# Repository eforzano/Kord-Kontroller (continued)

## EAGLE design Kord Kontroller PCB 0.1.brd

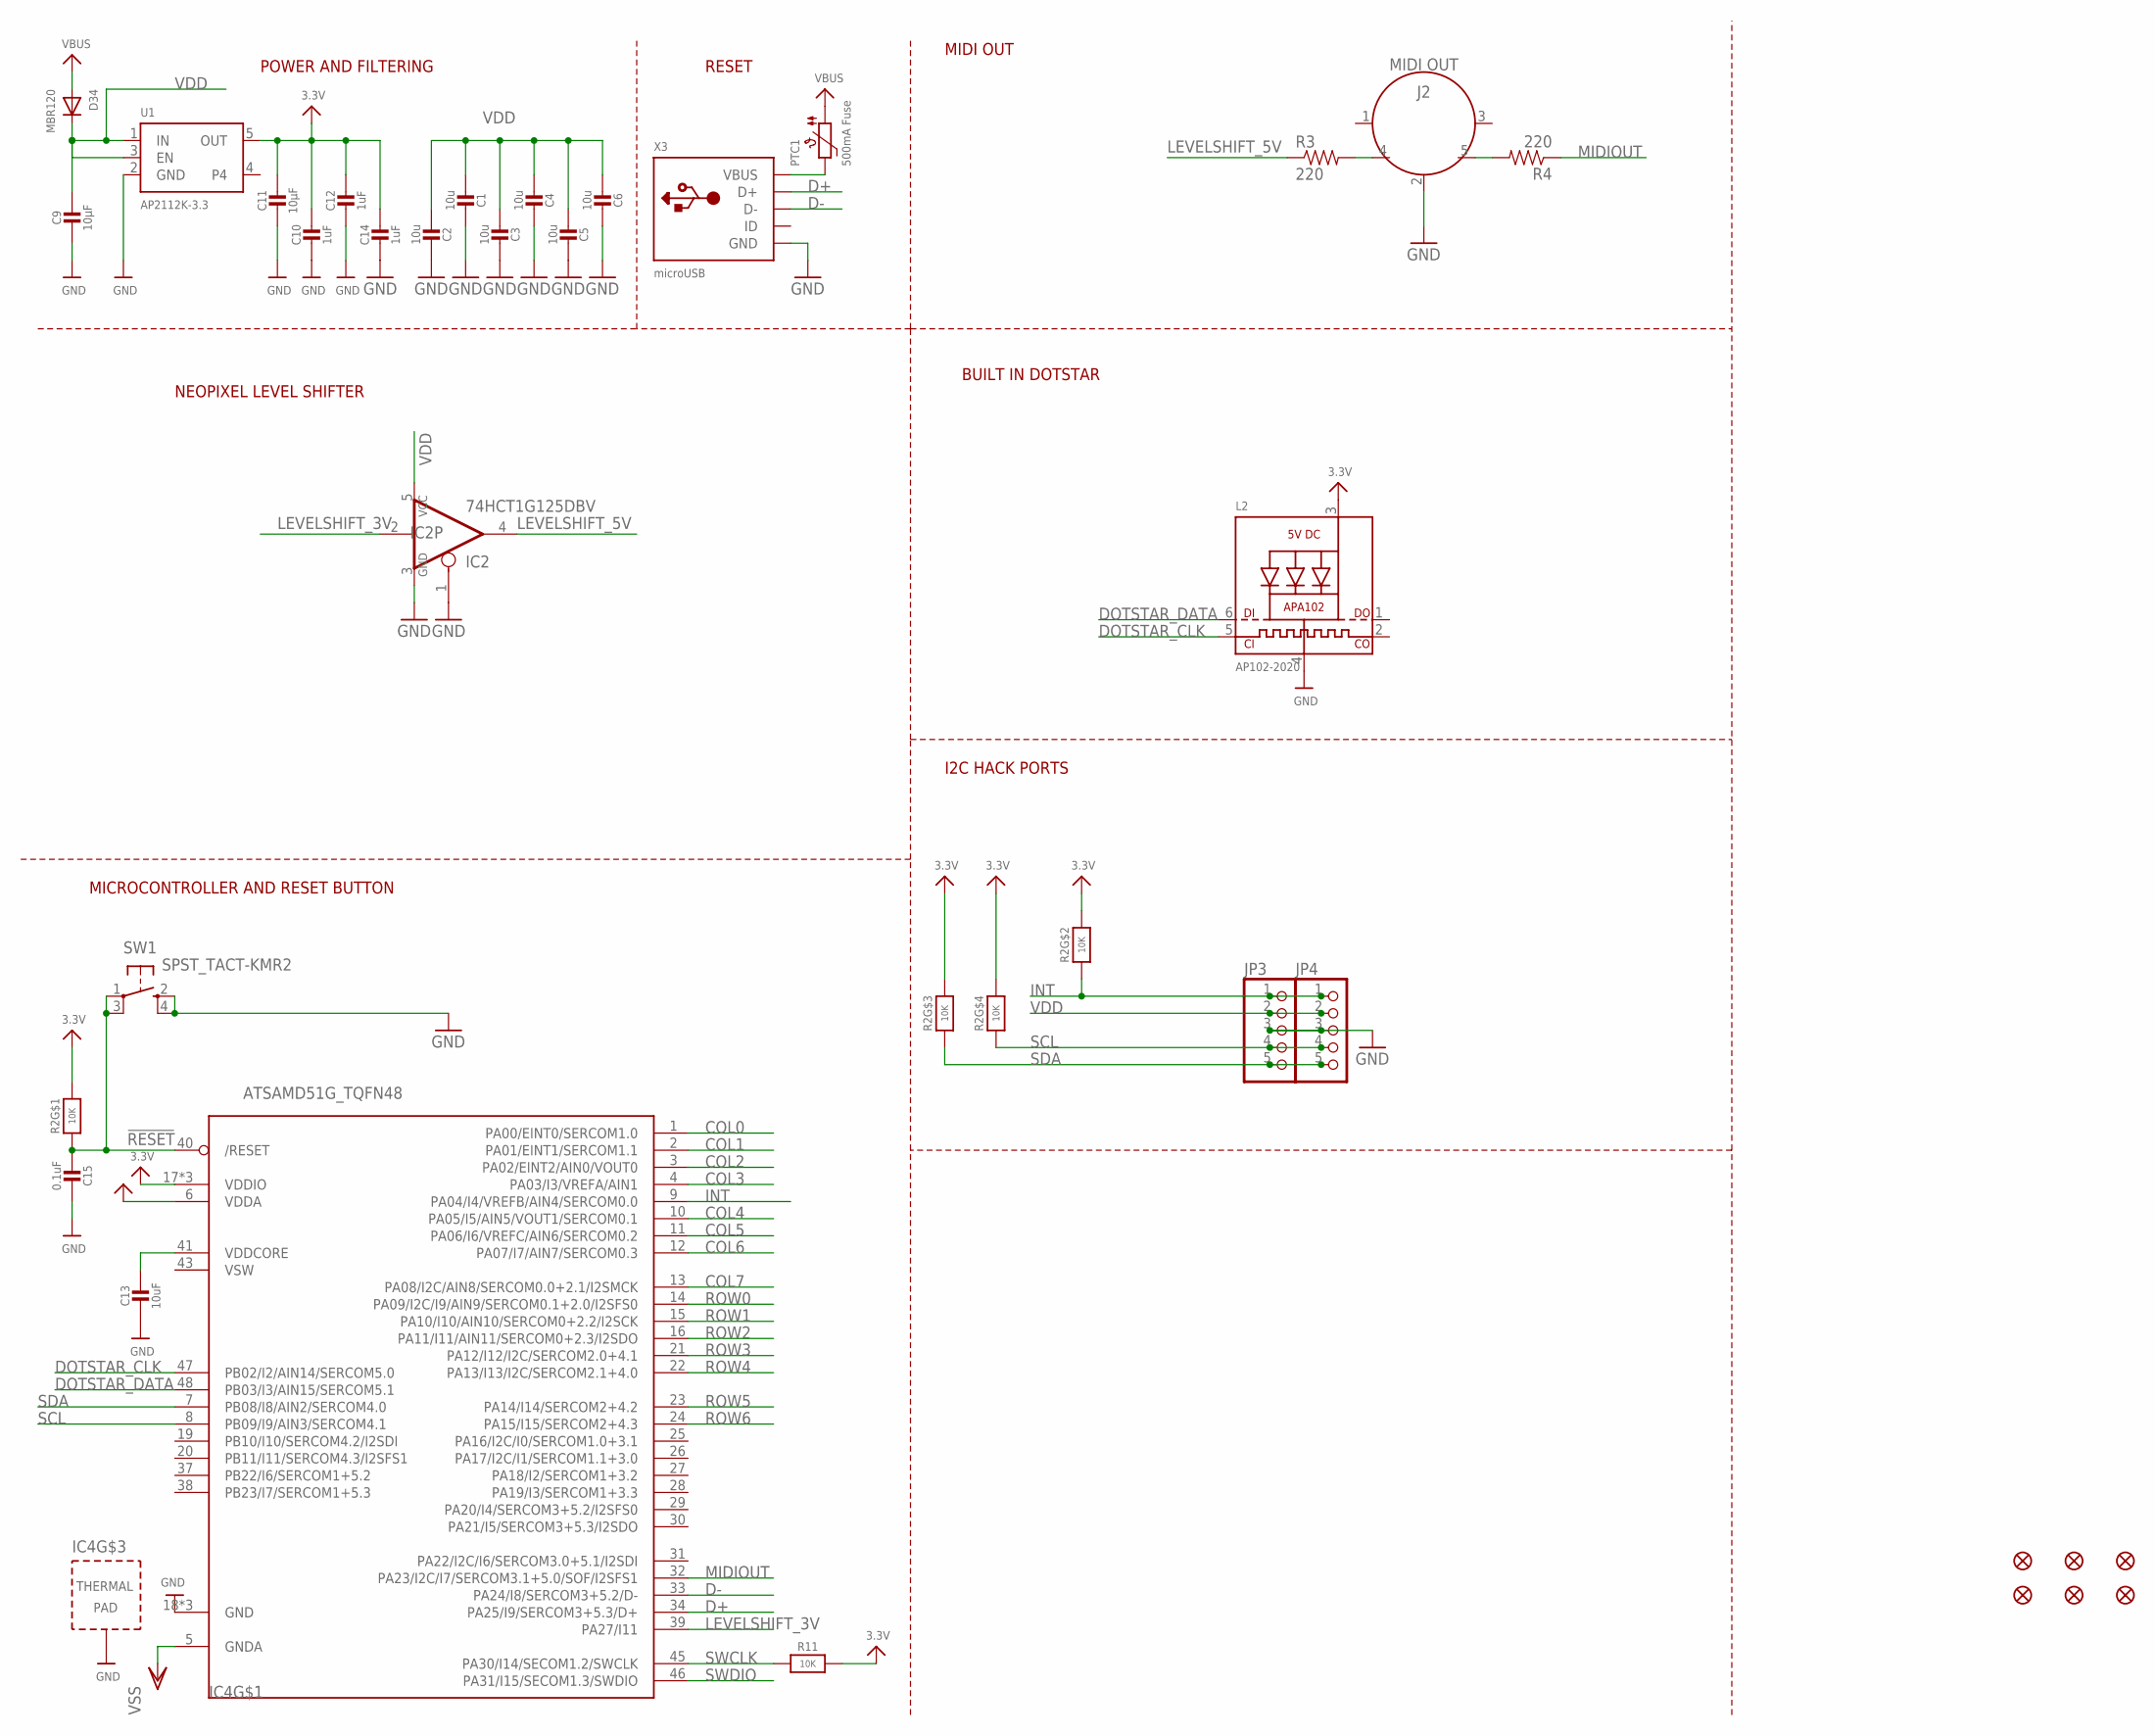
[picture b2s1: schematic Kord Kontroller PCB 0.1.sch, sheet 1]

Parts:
C1, C2, C3, C4, C5, C6: 10u; 0805-NO
C9, C11: 10µF; 0805-NO
C10, C12, C14: 1uF; 0603-NO
C13: 10uF; 0805-NO
C15: 0.1uF; 0603-NO
D34: MBR120; SOD-123FL
FID1, FID2, FID3, FID4, FID5, FID6: FIDUCIAL_1MM
IC2: 74HCT1G125DBV; SOT23-5
IC4: ATSAMD51G_TQFN48; TQFN48_7MM
J2: MIDI OUT; 5-PIN-DIN-RA-PCB-NEW
JP3, JP4: HEADER-1X5EDGESMT; 5P_EDGECONNECT
L2: AP102-2020; APA102_2020
PTC1: 500mA Fuse; 1206
R2: 10K; RESPACK_4X0603
R3, R4: 220; 0603-RES
R11: 10K; 0603-NO
SW1: SPST_TACT-KMR2; KMR2
U1: AP2112K-3.3; SOT23-5
X3: microUSB; 4UCONN_20329_NARROW

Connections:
3.3V: C10.1, C11.1, C12.1, C14.1, IC4.17 (VDDIO), IC4.36 (VDDIO), IC4.44 (VDDIO), L2.3 (VDD), R2.5 (2), R2.6 (2), R2.7 (2), R2.8 (2), R11.2, U1.5 (OUT)
!RESET: C15.2, IC4.40 (/RESET), R2.1, SW1.1, SW1.3 (P1)
AVDD: IC4.6 (VDDA)
COL0: IC4.1 (PA00/EINT0/SERCOM1.0); also elsewhere on the board
COL1: IC4.2 (PA01/EINT1/SERCOM1.1); also elsewhere on the board
COL2: IC4.3 (PA02/EINT2/AIN0/VOUT0); also elsewhere on the board
COL3: IC4.4 (PA03/I3/VREFA/AIN1); also elsewhere on the board
COL4: IC4.10 (PA05/I5/AIN5/VOUT1/SERCOM0.1); also elsewhere on the board
COL5: IC4.11 (PA06/I6/VREFC/AIN6/SERCOM0.2); also elsewhere on the board
COL6: IC4.12 (PA07/I7/AIN7/SERCOM0.3); also elsewhere on the board
COL7: IC4.13 (PA08/I2C/AIN8/SERCOM0.0+2.1/I2SMCK); also elsewhere on the board
D+: IC4.34 (PA25/I9/SERCOM3+5.3/D+), X3.D+
D-: IC4.33 (PA24/I8/SERCOM3+5.2/D-), X3.D-
DOTSTAR_CLK: IC4.47 (PB02/I2/AIN14/SERCOM5.0), L2.5 (CKI)
DOTSTAR_DATA: IC4.48 (PB03/I3/AIN15/SERCOM5.1), L2.6 (DI)
GND: C1.1, C2.1, C3.1, C4.1, C5.1, C6.1, C9.2, C10.2, C11.2, C12.2, C13.2, C14.2, C15.1, IC2.1 (OE), IC2.3 (GND), IC4.18 (GND), IC4.35 (GND), IC4.42 (GND), IC4.THERMAL (TP), J2.2, JP3.3, JP4.3, L2.4 (GND), SW1.2 (S), SW1.4 (S1), U1.2 (GND), X3.BASE@1 (GND), X3.BASE@2 (GND), X3.GND, X3.SPRT@1 (GND), X3.SPRT@2 (GND), X3.SPRT@3 (GND), X3.SPRT@4 (GND); also elsewhere on the board
INT: IC4.9 (PA04/I4/VREFB/AIN4/SERCOM0.0), JP3.1, JP4.1, R2.2 (1)
unnamed: PTC1.2, X3.VBUS
NEOPIXEL_3V: IC2.2 (I), IC4.39 (PA27/I11); also elsewhere on the board
unnamed: IC2.4 (O), R3.1
unnamed: J2.4, R3.2
unnamed: J2.5, R4.2
unnamed: IC4.32 (PA23/I2C/I7/SERCOM3.1+5.0/SOF/I2SFS1), R4.1
ROW0: IC4.14 (PA09/I2C/I9/AIN9/SERCOM0.1+2.0/I2SFS0); also elsewhere on the board
ROW1: IC4.15 (PA10/I10/AIN10/SERCOM0+2.2/I2SCK); also elsewhere on the board
ROW2: IC4.16 (PA11/I11/AIN11/SERCOM0+2.3/I2SDO); also elsewhere on the board
ROW3: IC4.21 (PA12/I12/I2C/SERCOM2.0+4.1); also elsewhere on the board
ROW4: IC4.22 (PA13/I13/I2C/SERCOM2.1+4.0); also elsewhere on the board
ROW5: IC4.23 (PA14/I14/SERCOM2+4.2); also elsewhere on the board
ROW6: IC4.24 (PA15/I15/SERCOM2+4.3); also elsewhere on the board
SCL: IC4.8 (PB09/I9/AIN3/SERCOM4.1), JP3.4, JP4.4, R2.4 (1)
SDA: IC4.7 (PB08/I8/AIN2/SERCOM4.0), JP3.5, JP4.5, R2.3 (1)
SWCLK: IC4.45 (PA30/I14/SECOM1.2/SWCLK), R11.1
SWDIO: IC4.46 (PA31/I15/SECOM1.3/SWDIO)
VBUS: D34.A, PTC1.1
VDD: C1.2, C2.2, C3.2, C4.2, C5.2, C6.2, C9.1, D34.C, IC2.5 (VCC), JP3.2, JP4.2, U1.1 (IN), U1.3 (EN); also elsewhere on the board
VDDCORE: C13.1, IC4.41 (VDDCORE)
VSS: IC4.5 (GNDA)
VSW: IC4.43 (VSW)

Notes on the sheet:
POWER AND FILTERING
RESET
BUILT IN DOTSTAR
I2C HACK PORTS
MICROCONTROLLER AND RESET BUTTON
MIDI OUT
NEOPIXEL LEVEL SHIFTER

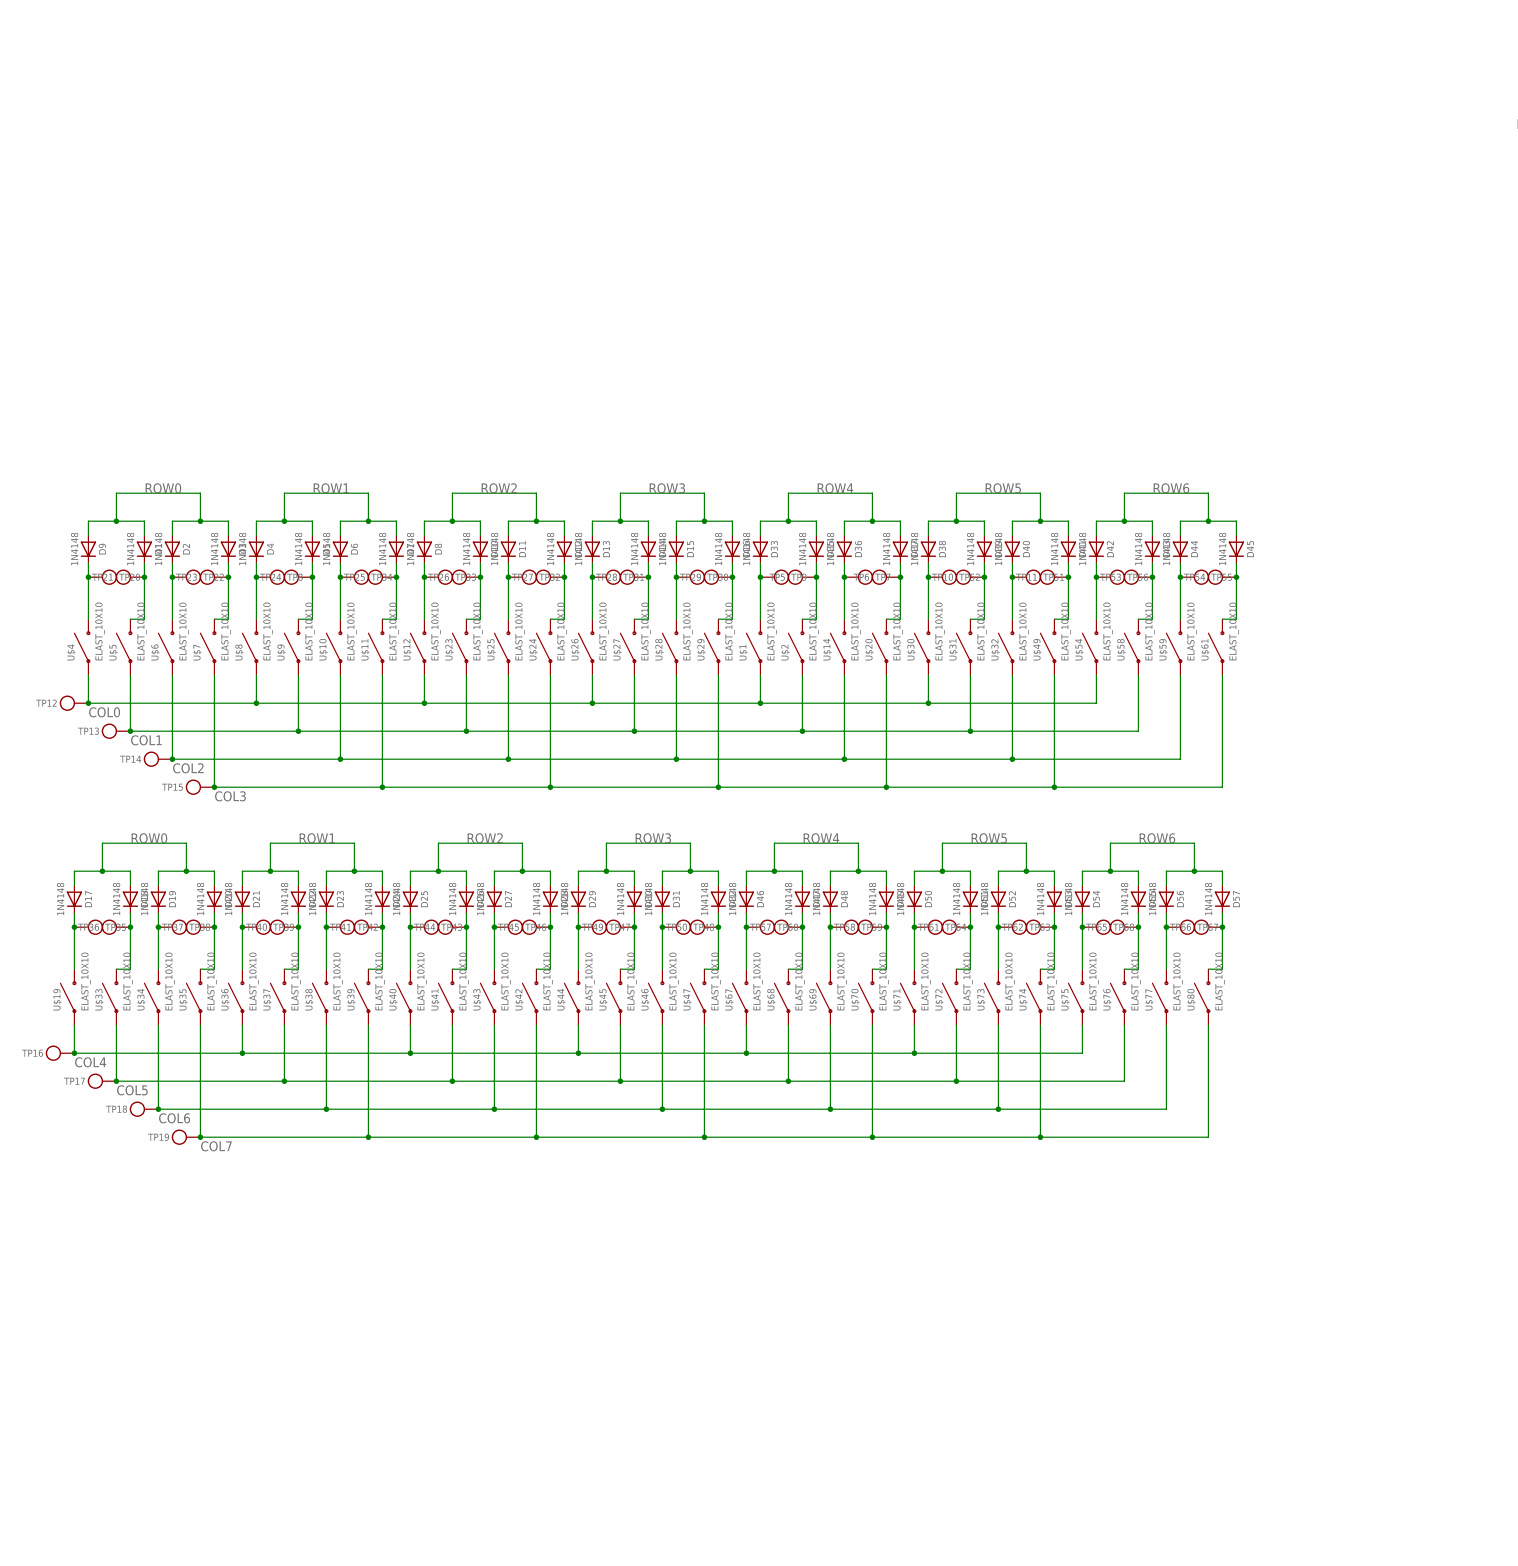
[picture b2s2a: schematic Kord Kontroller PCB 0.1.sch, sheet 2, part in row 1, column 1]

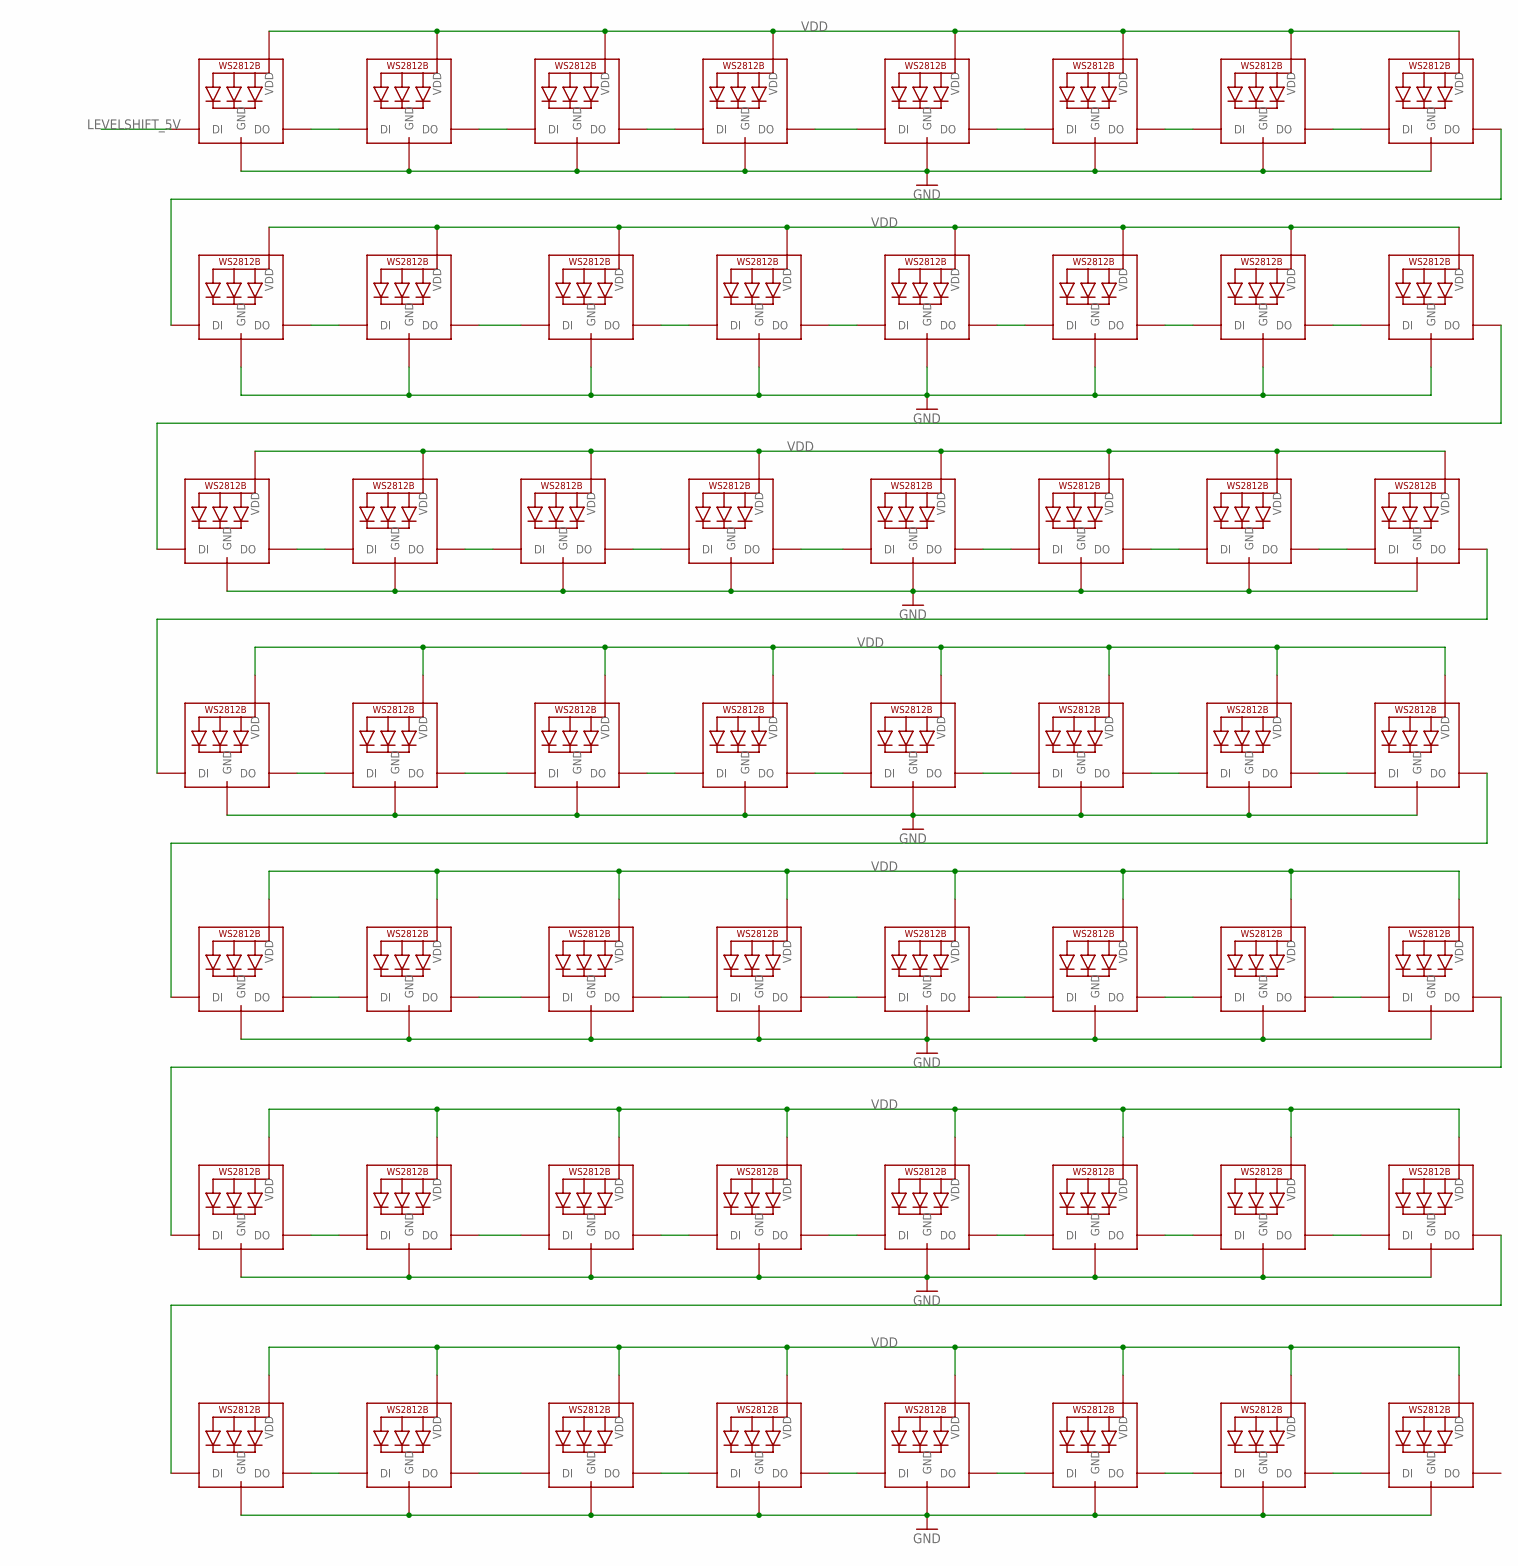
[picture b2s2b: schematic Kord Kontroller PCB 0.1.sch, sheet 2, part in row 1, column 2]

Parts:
D1, D2, D3, D4, D5, D6, D7, D8, D9, D10, D11, D12, D13, D14, D15, D16, D17, D18, D19, D20, D21, D22, D23, D24, D25, D26, D27, D28, D29, D30, D31, D32, D33, D35, D36, D37, D38, D39, D40, D41, D42, D43, D44, D45, D46, D47, D48, D49, D50, D51, D52, D53, D54, D55, D56, D57: 1N4148; SOD-323
LED1, LED2, LED3, LED4, LED5, LED6, LED7, LED8, LED9, LED10, LED11, LED12, LED13, LED14, LED15, LED16, LED17, LED18, LED19, LED20, LED21, LED22, LED23, LED24, LED25, LED26, LED27, LED28, LED29, LED30, LED31, LED32, LED33, LED34, LED35, LED36, LED37, LED38, LED39, LED40, LED41, LED42, LED43, LED44, LED45, LED46, LED47, LED48, LED49, LED50, LED51, LED52, LED53, LED54, LED55, LED56: WS2812B3535; LED3535
TP5, TP6, TP7, TP8, TP9, TP10, TP11, TP12, TP13, TP14, TP15, TP16, TP17, TP18, TP19, TP20, TP21, TP22, TP23, TP24, TP25, TP26, TP27, TP28, TP29, TP30, TP31, TP32, TP33, TP34, TP35, TP36, TP37, TP38, TP39, TP40, TP41, TP42, TP43, TP44, TP45, TP46, TP47, TP48, TP49, TP50, TP51, TP52, TP53, TP54, TP55, TP56, TP57, TP58, TP59, TP60, TP61, TP62, TP63, TP64, TP65, TP66, TP67, TP68: TESTPOINTROUND1.5MM; TESTPOINT_ROUND_1.5MM
U$1, U$2, U$4, U$5, U$6, U$7, U$8, U$9, U$10, U$11, U$12, U$14, U$19, U$20, U$23, U$24, U$25, U$26, U$27, U$28, U$29, U$30, U$31, U$32, U$33, U$34, U$35, U$36, U$37, U$38, U$39, U$40, U$41, U$42, U$43, U$44, U$45, U$46, U$47, U$49, U$54, U$58, U$59, U$61, U$67, U$68, U$69, U$70, U$71, U$72, U$73, U$74, U$75, U$76, U$77, U$80: ELAST_10X10; ELAST_PAD_SQUARE_10MM_4X4WIDE

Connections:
COL0: TP12.P$1, U$1.P$1, U$4.P$1, U$8.P$1, U$12.P$1, U$26.P$1, U$30.P$1, U$54.P$1; also elsewhere on the board
COL1: TP13.P$1, U$2.P$1, U$5.P$1, U$9.P$1, U$23.P$1, U$27.P$1, U$31.P$1, U$58.P$1; also elsewhere on the board
COL2: TP14.P$1, U$6.P$1, U$10.P$1, U$14.P$1, U$25.P$1, U$28.P$1, U$32.P$1, U$59.P$1; also elsewhere on the board
COL3: TP15.P$1, U$7.P$1, U$11.P$1, U$20.P$1, U$24.P$1, U$29.P$1, U$49.P$1, U$61.P$1; also elsewhere on the board
COL4: TP16.P$1, U$19.P$1, U$36.P$1, U$40.P$1, U$44.P$1, U$67.P$1, U$71.P$1, U$75.P$1; also elsewhere on the board
COL5: TP17.P$1, U$33.P$1, U$37.P$1, U$41.P$1, U$45.P$1, U$68.P$1, U$72.P$1, U$76.P$1; also elsewhere on the board
COL6: TP18.P$1, U$34.P$1, U$38.P$1, U$43.P$1, U$46.P$1, U$69.P$1, U$73.P$1, U$77.P$1; also elsewhere on the board
COL7: TP19.P$1, U$35.P$1, U$39.P$1, U$42.P$1, U$47.P$1, U$70.P$1, U$74.P$1, U$80.P$1; also elsewhere on the board
GND: LED1.4 (GND), LED2.4 (GND), LED3.4 (GND), LED4.4 (GND), LED5.4 (GND), LED6.4 (GND), LED7.4 (GND), LED8.4 (GND), LED9.4 (GND), LED10.4 (GND), LED11.4 (GND), LED12.4 (GND), LED13.4 (GND), LED14.4 (GND), LED15.4 (GND), LED16.4 (GND), LED17.4 (GND), LED18.4 (GND), LED19.4 (GND), LED20.4 (GND), LED21.4 (GND), LED22.4 (GND), LED23.4 (GND), LED24.4 (GND), LED25.4 (GND), LED26.4 (GND), LED27.4 (GND), LED28.4 (GND), LED29.4 (GND), LED30.4 (GND), LED31.4 (GND), LED32.4 (GND), LED33.4 (GND), LED34.4 (GND), LED35.4 (GND), LED36.4 (GND), LED37.4 (GND), LED38.4 (GND), LED39.4 (GND), LED40.4 (GND), LED41.4 (GND), LED42.4 (GND), LED43.4 (GND), LED44.4 (GND), LED45.4 (GND), LED46.4 (GND), LED47.4 (GND), LED48.4 (GND), LED49.4 (GND), LED50.4 (GND), LED51.4 (GND), LED52.4 (GND), LED53.4 (GND), LED54.4 (GND), LED55.4 (GND), LED56.4 (GND); also elsewhere on the board
unnamed: D33.C, TP9.P$1, U$1.P$2
unnamed: D9.C, TP20.P$1, U$4.P$2
unnamed: D1.C, TP21.P$1, U$5.P$2
unnamed: D2.C, TP22.P$1, U$6.P$2
unnamed: D3.C, TP23.P$1, U$7.P$2
unnamed: D4.C, TP8.P$1, U$8.P$2
unnamed: LED17.3 (DO), LED18.1 (DI)
unnamed: LED18.3 (DO), LED19.1 (DI)
unnamed: D5.C, TP24.P$1, U$9.P$2
unnamed: LED19.3 (DO), LED20.1 (DI)
unnamed: LED1.3 (DO), LED2.1 (DI)
unnamed: LED2.3 (DO), LED3.1 (DI)
unnamed: LED3.3 (DO), LED4.1 (DI)
unnamed: LED4.3 (DO), LED5.1 (DI)
unnamed: D6.C, TP34.P$1, U$10.P$2
unnamed: LED5.3 (DO), LED6.1 (DI)
unnamed: LED6.3 (DO), LED7.1 (DI)
unnamed: D7.C, TP25.P$1, U$11.P$2
unnamed: LED7.3 (DO), LED8.1 (DI)
unnamed: D8.C, TP33.P$1, U$12.P$2
unnamed: LED8.3 (DO), LED9.1 (DI)
unnamed: D10.C, TP26.P$1, U$23.P$2
unnamed: D11.C, TP32.P$1, U$25.P$2
unnamed: D12.C, TP27.P$1, U$24.P$2
unnamed: D13.C, TP31.P$1, U$26.P$2
unnamed: D14.C, TP28.P$1, U$27.P$2
unnamed: D15.C, TP30.P$1, U$28.P$2
unnamed: D16.C, TP29.P$1, U$29.P$2
unnamed: LED9.3 (DO), LED10.1 (DI)
unnamed: LED10.3 (DO), LED12.1 (DI)
unnamed: LED11.1 (DI), LED12.3 (DO)
unnamed: LED11.3 (DO), LED13.1 (DI)
unnamed: LED13.3 (DO), LED14.1 (DI)
unnamed: LED14.3 (DO), LED15.1 (DI)
unnamed: LED15.3 (DO), LED16.1 (DI)
unnamed: LED20.3 (DO), LED21.1 (DI)
unnamed: LED21.3 (DO), LED22.1 (DI)
unnamed: LED22.3 (DO), LED23.1 (DI)
unnamed: LED23.3 (DO), LED24.1 (DI)
unnamed: LED24.3 (DO), LED25.1 (DI)
unnamed: LED25.3 (DO), LED26.1 (DI)
unnamed: LED26.3 (DO), LED28.1 (DI)
unnamed: LED27.1 (DI), LED28.3 (DO)
unnamed: LED27.3 (DO), LED29.1 (DI)
unnamed: LED29.3 (DO), LED30.1 (DI)
unnamed: LED30.3 (DO), LED31.1 (DI)
unnamed: LED31.3 (DO), LED32.1 (DI)
unnamed: D17.C, TP35.P$1, U$19.P$2
unnamed: D18.C, TP36.P$1, U$33.P$2
unnamed: D19.C, TP38.P$1, U$34.P$2
unnamed: D20.C, TP37.P$1, U$35.P$2
unnamed: D21.C, TP39.P$1, U$36.P$2
unnamed: D22.C, TP40.P$1, U$37.P$2
unnamed: D23.C, TP42.P$1, U$38.P$2
unnamed: D24.C, TP41.P$1, U$39.P$2
unnamed: D25.C, TP43.P$1, U$40.P$2
unnamed: D26.C, TP44.P$1, U$41.P$2
unnamed: D27.C, TP46.P$1, U$43.P$2
unnamed: D28.C, TP45.P$1, U$42.P$2
unnamed: D29.C, TP47.P$1, U$44.P$2
unnamed: D30.C, TP49.P$1, U$45.P$2
unnamed: D31.C, TP48.P$1, U$46.P$2
unnamed: D32.C, TP50.P$1, U$47.P$2
unnamed: LED16.3 (DO), LED17.1 (DI)
unnamed: D35.C, TP5.P$1, U$2.P$2
unnamed: D36.C, TP7.P$1, U$14.P$2
unnamed: D37.C, TP6.P$1, U$20.P$2
unnamed: D38.C, TP52.P$1, U$30.P$2
unnamed: D39.C, TP10.P$1, U$31.P$2
unnamed: D40.C, TP51.P$1, U$32.P$2
unnamed: D41.C, TP11.P$1, U$49.P$2
unnamed: D42.C, TP56.P$1, U$54.P$2
unnamed: D43.C, TP53.P$1, U$58.P$2
unnamed: D44.C, TP55.P$1, U$59.P$2
unnamed: D45.C, TP54.P$1, U$61.P$2
unnamed: D46.C, TP60.P$1, U$67.P$2
unnamed: D47.C, TP57.P$1, U$68.P$2
unnamed: D48.C, TP59.P$1, U$69.P$2
unnamed: D49.C, TP58.P$1, U$70.P$2
unnamed: D50.C, TP64.P$1, U$71.P$2
unnamed: D51.C, TP61.P$1, U$72.P$2
unnamed: D52.C, TP63.P$1, U$73.P$2
unnamed: D53.C, TP62.P$1, U$74.P$2
unnamed: D54.C, TP68.P$1, U$75.P$2
unnamed: D55.C, TP65.P$1, U$76.P$2
unnamed: D56.C, TP67.P$1, U$77.P$2
unnamed: D57.C, TP66.P$1, U$80.P$2
unnamed: LED33.3 (DO), LED34.1 (DI)
unnamed: LED34.3 (DO), LED36.1 (DI)
unnamed: LED35.1 (DI), LED36.3 (DO)
unnamed: LED35.3 (DO), LED37.1 (DI)
unnamed: LED37.3 (DO), LED38.1 (DI)
unnamed: LED38.3 (DO), LED39.1 (DI)
unnamed: LED39.3 (DO), LED40.1 (DI)
unnamed: LED41.3 (DO), LED42.1 (DI)
unnamed: LED42.3 (DO), LED44.1 (DI)
unnamed: LED43.1 (DI), LED44.3 (DO)
unnamed: LED43.3 (DO), LED45.1 (DI)
unnamed: LED45.3 (DO), LED46.1 (DI)
unnamed: LED46.3 (DO), LED47.1 (DI)
unnamed: LED47.3 (DO), LED48.1 (DI)
unnamed: LED49.3 (DO), LED50.1 (DI)
unnamed: LED50.3 (DO), LED52.1 (DI)
unnamed: LED51.1 (DI), LED52.3 (DO)
unnamed: LED51.3 (DO), LED53.1 (DI)
unnamed: LED53.3 (DO), LED54.1 (DI)
unnamed: LED54.3 (DO), LED55.1 (DI)
unnamed: LED55.3 (DO), LED56.1 (DI)
unnamed: LED40.3 (DO), LED41.1 (DI)
unnamed: LED48.3 (DO), LED49.1 (DI)
unnamed: LED32.3 (DO), LED33.1 (DI)
NEOPIXEL_5V: LED1.1 (DI); also elsewhere on the board
ROW0: D1.A, D2.A, D3.A, D9.A, D17.A, D18.A, D19.A, D20.A; also elsewhere on the board
ROW1: D4.A, D5.A, D6.A, D7.A, D21.A, D22.A, D23.A, D24.A; also elsewhere on the board
ROW2: D8.A, D10.A, D11.A, D12.A, D25.A, D26.A, D27.A, D28.A; also elsewhere on the board
ROW3: D13.A, D14.A, D15.A, D16.A, D29.A, D30.A, D31.A, D32.A; also elsewhere on the board
ROW4: D33.A, D35.A, D36.A, D37.A, D46.A, D47.A, D48.A, D49.A; also elsewhere on the board
ROW5: D38.A, D39.A, D40.A, D41.A, D50.A, D51.A, D52.A, D53.A; also elsewhere on the board
ROW6: D42.A, D43.A, D44.A, D45.A, D54.A, D55.A, D56.A, D57.A; also elsewhere on the board
VDD: LED1.2 (VDD), LED2.2 (VDD), LED3.2 (VDD), LED4.2 (VDD), LED5.2 (VDD), LED6.2 (VDD), LED7.2 (VDD), LED8.2 (VDD), LED9.2 (VDD), LED10.2 (VDD), LED11.2 (VDD), LED12.2 (VDD), LED13.2 (VDD), LED14.2 (VDD), LED15.2 (VDD), LED16.2 (VDD), LED17.2 (VDD), LED18.2 (VDD), LED19.2 (VDD), LED20.2 (VDD), LED21.2 (VDD), LED22.2 (VDD), LED23.2 (VDD), LED24.2 (VDD), LED25.2 (VDD), LED26.2 (VDD), LED27.2 (VDD), LED28.2 (VDD), LED29.2 (VDD), LED30.2 (VDD), LED31.2 (VDD), LED32.2 (VDD), LED33.2 (VDD), LED34.2 (VDD), LED35.2 (VDD), LED36.2 (VDD), LED37.2 (VDD), LED38.2 (VDD), LED39.2 (VDD), LED40.2 (VDD), LED41.2 (VDD), LED42.2 (VDD), LED43.2 (VDD), LED44.2 (VDD), LED45.2 (VDD), LED46.2 (VDD), LED47.2 (VDD), LED48.2 (VDD), LED49.2 (VDD), LED50.2 (VDD), LED51.2 (VDD), LED52.2 (VDD), LED53.2 (VDD), LED54.2 (VDD), LED55.2 (VDD), LED56.2 (VDD); also elsewhere on the board

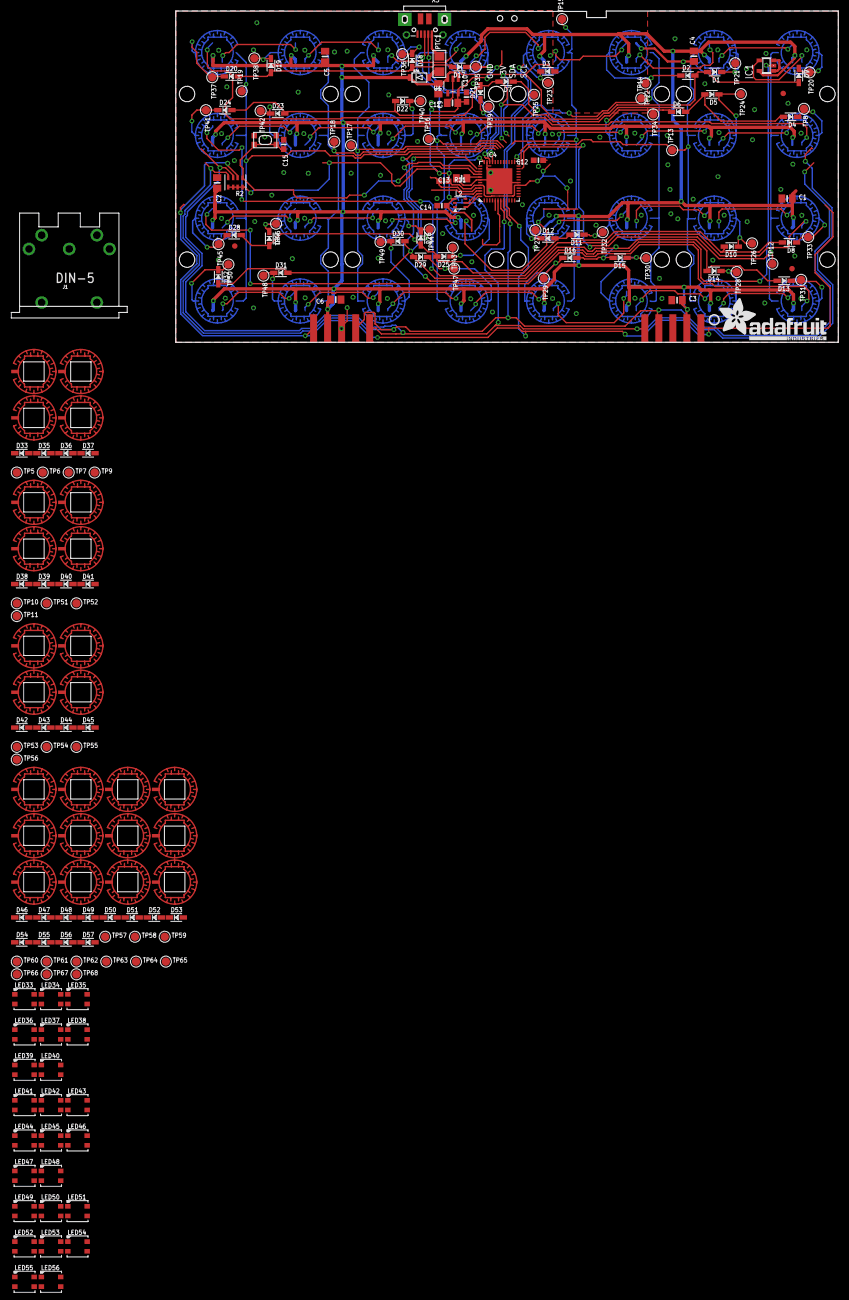
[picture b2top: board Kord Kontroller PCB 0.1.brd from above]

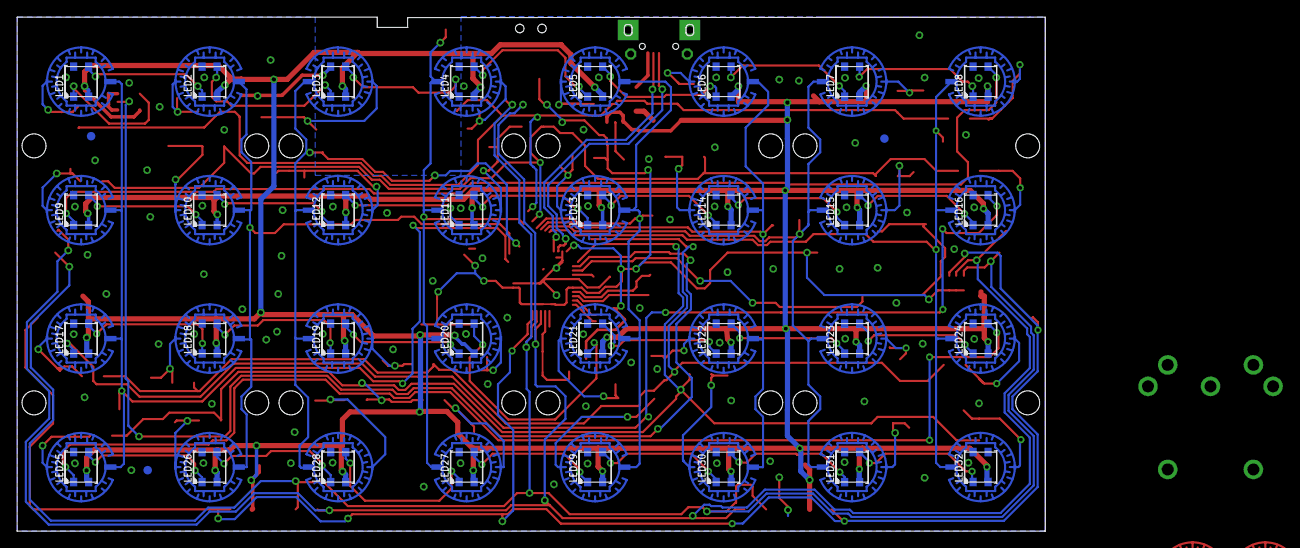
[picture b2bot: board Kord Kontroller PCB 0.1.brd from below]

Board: 2 copper layers, 120.0 x 60.0 mm, 267 parts (67 on the bottom side), 143 nets.

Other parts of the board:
IC1: 74HCT1G125DBV; SOT23-5
J1: DIN5; DIN5-RA-PTH
U$3: ADAFRUIT_TEXT_20MM
U$48: TRELLISLOGO
U$78: PCBFEAT-REV-040

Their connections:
GND: IC1.1, IC1.3; also elsewhere on the board
NEOPIXEL_3V: IC1.2; also elsewhere on the board
NEOPIXEL_5V: IC1.4; also elsewhere on the board
VDD: IC1.5; also elsewhere on the board

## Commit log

2019-07-23 Adding board and schematics
2019-07-23 adding board and schematic
2019-08-05 Added lines to new 64-QFN part
2019-08-07 Deleted TQFN8 pin package for 64 pin package
2019-08-20 traced routes for LEDs and half the board
2019-08-28 Added Routes for Cols 0-6, Finished Rows and diodes
2019-08-29 Added traces for 7-14
2019-08-29 added last top button diodes
2019-09-01 routed power and midi
2019-09-02 Finished Routinggit status
2019-09-07 Added VDD plane and GND plane
2019-09-08 Update README.md
    Added some more clear verbiage
2019-09-08 cleaned up 90 degrees and vias
2019-09-29 Switched pieces to bottom
2019-10-04 Added osc and reourting diodes
2019-10-05 Moved resistors to bottom and Added 32k crystal
2019-10-05 Moved resistor a little
2019-10-05 added a logo
2019-10-05 Minor resistor change
2019-10-06 moved some stuff around
2019-10-17 Rotated LEDs to remove DRC errors
2019-11-24 Removed wire stubs
2019-12-26 Changed USB package and removed most of the errorsgit stash
2020-01-06 Removed AIRWIRE
2020-01-07 FINAL SENT
2020-01-07 FINAL SENT first board
2020-01-09 changed crystal
2020-01-09 Level shifter and decouplers
2020-01-10 Rerouted, gave better routes, switched voltage shifter part
2020-01-10 Moved caps
2020-01-10 Fixed some right angle traces
2020-01-10 3.3 v missing trace
2020-01-10 Board REV A
2020-02-11 Rev B and stuff on the right side
2020-05-03 LED Variant and rewire
2020-05-28 Moved to add holes
2020-06-21 added 2.5 mmtrs parts
2021-07-30 Added Capacitors for power management
2021-08-01 REV-B
